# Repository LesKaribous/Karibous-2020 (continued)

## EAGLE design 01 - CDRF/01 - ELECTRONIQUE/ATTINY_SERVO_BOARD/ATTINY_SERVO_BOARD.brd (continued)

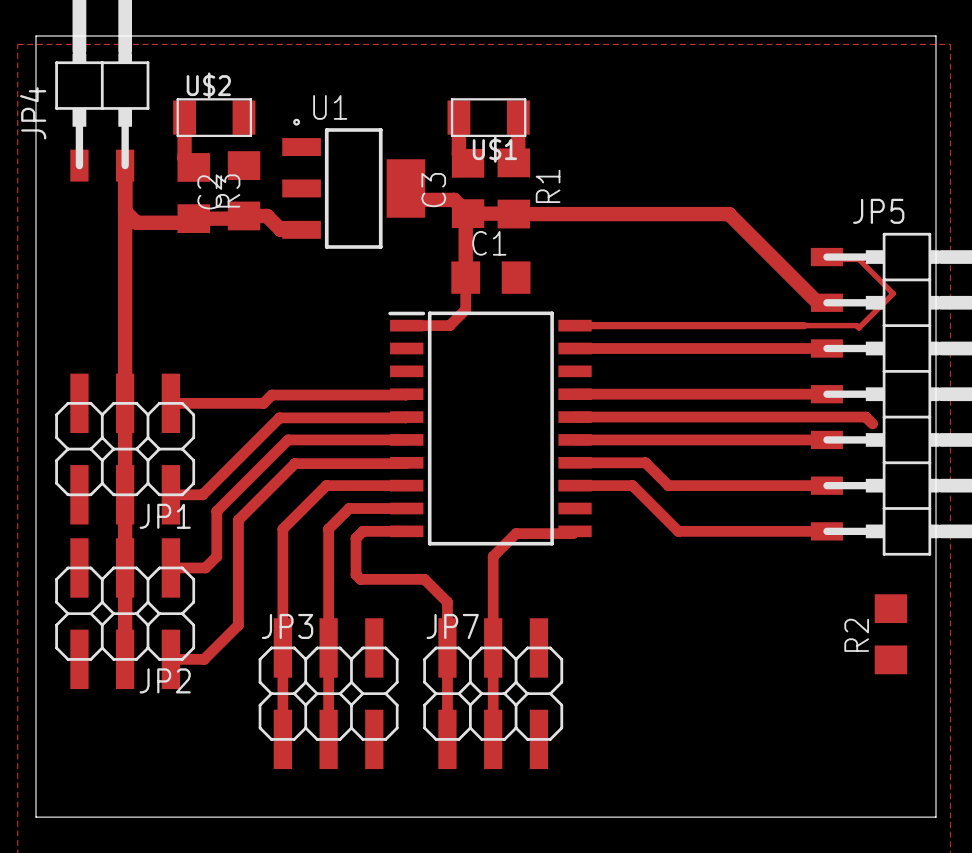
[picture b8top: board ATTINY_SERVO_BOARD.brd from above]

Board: 2 copper layers, 50.0 x 43.4 mm, 16 parts (0 on the bottom side), 19 nets.

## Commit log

2019-10-06 first version
2019-10-06 PCB - update
2019-10-07 Update
    Change P-MOSFET by N-MOSFET
2019-10-10 update 3D packages
2019-10-25 create
2019-10-25 routage
2020-01-19 update pcb pump
2020-01-31 first update
2020-02-10 update name
2020-02-10 Archive 2019
    Archive 2019 pour faire les essais du code 2020
2020-03-07 Class BRAS
2020-03-07 delete
2020-03-07 Clean up
2020-03-07 add servo drapeau
2020-03-14 Release Classe IHM
2020-03-14 Creation Classe ComNavigation
2020-03-14 cleanup
2020-03-14 init Job
2020-03-15 Setting up
2020-03-15 tiens
2020-03-15 WIP Planner
2020-03-15 Main routine
2020-03-16 planMove
2020-03-16 behavior
2020-03-25 Setting up planner with classy class
2020-03-25 Add JeVois code
2020-03-27 getting clean ?
2020-04-24 :sparkles: new
2020-05-01 Com de la fonction attente | Attente planner
2020-05-01 Add elevator function v0.1
2020-05-18 update pcb
2020-05-23 update GUI
2020-05-30 update nav
2020-05-30 Enum
2020-06-22 update elec
2020-06-26 electrical update
2020-10-09 First
2020-10-12 update opponent detection
2020-10-12 simplify commands
2020-10-12 opponent detection
2020-10-14 add opponent detection
2020-10-17 prepare absolute position
2020-10-17 clean state machine
2020-10-22 add .vscode
2020-11-28 beta pcb arm serial
2020-11-30 test proto ihm robot
2020-11-30 absolute implementation
2020-11-30 Change for new electronic
2020-11-30 change switch state
2020-11-30 debug typo error
2020-11-30 Update IHM
2020-11-30 add test lines
2020-12-01 new freq
2020-12-01 implemente ABS position
2020-12-09 add cap and led
2020-12-09 update board
2020-12-13 Fisrt version laser
